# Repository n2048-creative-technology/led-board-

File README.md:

# LED board

A wall of **584 addressable pixels** — eight identical segments of 73 — that
fills with light one pixel at a time, then breathes. A Seeed XIAO ESP32C3 on a
custom 24 V driver board runs all eight segments from a single hardware timer,
and raises its own Wi-Fi access point so colour, timing and power budget can be
changed from a phone with no app and no internet.

| | |
|---|---|
| Controller | Seeed Studio XIAO ESP32C3 on the `otherworlds-v2` driver board |
| Output | 8 segments × 73 px = **584** WS281x, colour order GBR, 800 kHz, 24 V |
| Frame rate | **63 fps** with the access point running |
| Control | Wi-Fi AP `LED-Board` / `ledboard` → <http://4.3.2.1/> |
| Persistence | All settings in NVS, survive a power cycle |

---

## Contents

- [How it behaves](#how-it-behaves)
- [Web UI](#web-ui)
- [HTTP API](#http-api)
- [Driving 8 outputs from a 2-channel chip](#driving-8-outputs-from-a-2-channel-chip)
- [The driver board](#the-driver-board)
- [Firmware hardware map](#firmware-hardware-map)
- [Power](#power)
- [Build, flash, monitor](#build-flash-monitor)
- [Repository layout](#repository-layout)
- [Status](#status)

---

## How it behaves

Power-up runs a two-stage sequence, identical and in step across all eight
segments:

1. **FILL** — the segment fades up pixel by pixel from the first to the last,
   with a soft leading edge spanning a settable number of pixels.
2. **BREATHE** — once full, brightness cycles between 100% and a settable floor,
   forever.

Turning the lights off runs the fill **backwards**: the pixels withdraw in
exactly the reverse order they arrived, so the last to light is the first to go
dark. Pressing off mid-sweep picks up at the matching front position rather than
snapping, so it stays smooth even if you change your mind halfway.

The pixel levels in that diagram are not an illustration — they are computed by
running the firmware's own integer maths (`renderFrontAt()`, `breatheWave()` and
NeoPixel's gamma-2.6 table) outside the chip. The fade is gamma-corrected so it
ramps evenly to the eye instead of spending most of its apparent brightness in
the first few percent.

## Web UI

The board raises its own access point with a captive portal. Join the network
and the "sign in to network" sheet should open the UI by itself; if not, browse
to the address.

| | |
|---|---|
| SSID | `LED-Board` |
| Password | `ledboard` |
| Address | <http://4.3.2.1/> |

Everything on the page is inline — no CDN is reachable on an access point — so
the colour wheel is drawn on a `<canvas>` rather than pulled from a library.

<p align="center">
  
  &nbsp;&nbsp;
  
</p>

<sub>Left: the page as served, at its 520 px maximum width. Right: the same page
at 390 px — it is a single responsive column, which is how it will actually be
used.</sub>

### Colour

An HSV wheel (drag to pick), R/G/B sliders, a hex field, and the OS-native
colour picker. All four stay in sync, and changes are pushed to the strip live,
debounced at ~60 ms.

### Breathing and start-up fill

Period runs 0.5–20 s; a floor of 100% holds steady with no breathing. *Replay
fill* restarts the fill animation so it can be watched again without a reboot.
Edge is how many pixels the leading fade spans — 1 is a hard wipe.

### Power

The budget, with live feedback on the resulting hold level and estimated draw.
The limiter accounts for the *current colour*: red lights one channel, yellow
two, white three, so the achievable brightness changes as you pick. Read
[Power](#power) before trusting the milliamp figure on this 24 V board.

<sub>The same card at a 3000 budget (left) and 15000 with a blue-ish colour
selected (right). Both numbers come from the firmware's own estimator.</sub>

### Access point — you cannot lock yourself out

Credentials are validated server-side before being stored: SSID 1–32 characters,
password empty for an open network or 8–63 characters. A 1–7 character password
is rejected, since no access point will start with one. On top of that, if a
stored pair ever fails to bring the AP up, the board falls back to `LED-Board` /
`ledboard` by itself. **Recovering never requires reflashing over USB.**

Applying restarts the radio, so the phone will drop off and must rejoin with the
new details. The HTTP reply is sent ~400 ms before the restart, so the browser
always sees the response.

### Saving

Changes apply live. **Save to board** writes them to NVS so they survive a power
cycle; without saving, the board reverts to its defaults on reboot — including
the on/off state, so a board saved "off" comes back off.

## HTTP API

Handy for scripting or an external controller. All values are clamped
server-side, so out-of-range input is safe.

| Endpoint | Purpose |
|---|---|
| `GET /api/state` | Current settings, hold level, estimated mA, fps, phase |
| `GET /api/set?r=&g=&b=&bp=&bm=&fd=&fe=&pb=` | Set any subset; returns the new state |
| `GET /api/power?on=0\|1` | Turn off (reverse withdraw) or on (fill) |
| `GET /api/ap?ssid=&pass=` | Change AP credentials; `400` if invalid |
| `GET /api/fill` | Restart the fill animation |
| `GET /api/save` | Persist current settings to NVS |

Parameters: `r` `g` `b` 0–255 · `bp` breathe period ms 200–120000 · `bm` breathe
floor % 0–100 · `fd` fill duration ms 100–120000 · `fe` fill edge px 1–73 ·
`pb` power budget 100–40000.

`phase` reports `filling`, `breathing`, `emptying` or `off`.

```console
$ curl "http://4.3.2.1/api/state"
{"on":true,"ssid":"LED-Board","pass":"ledboard","r":255,"g":255,"b":0,
 "bp":4000,"bm":80,"fd":4000,"fe":8,"pb":3000,"hold":31,"ma":2920,
 "maFull":23944,"fps":63,"phase":"breathing"}
```

Wi-Fi does not disturb the LED output — the strips are driven by the RMT
peripheral in hardware, and the frame rate stayed at 62–63 fps with the AP up
and a client connected.

## Driving 8 outputs from a 2-channel chip

The ESP32-C3 has only **2 RMT TX channels**, which rules out both obvious
approaches. The firmware instead transmits **one** segment's worth of data on a
single RMT channel bound to GPIO3, then uses the GPIO matrix
(`esp_rom_gpio_connect_out_signal`) to route that same output signal to the
other seven pins. Every segment gets an identical, hardware-timed waveform, and
a frame costs one transmission (~2.2 ms) instead of eight.

**The trade-off:** all 8 segments necessarily show the *same* content. That is
exactly what this piece wants. If independent per-segment animation is ever
needed, the options are:

- **2 independent strips** via FastLED (the chip's real RMT limit), or
- **8 independent strips** via a parallel bit-bang driver, computing an 8-bit
  GPIO mask per bit period — all eight pins live in one 32-bit output register,
  so this is feasible but needs cycle-accurate timing work, or
- **a chip with more RMT channels** — ESP32-S3 has 4, the original ESP32 has 8.

## The driver board

KiCad project: [`electronics/otherworlds-v2.kicad_pro`](electronics/otherworlds-v2.kicad_pro).
Two-layer, **98.7 × 90.9 mm**, 1.6 mm, four M4 mounting holes, through-hole
throughout so it can be built by hand.

<sub>Exported from
<a href="electronics/otherworlds-v2.kicad_sch">otherworlds-v2.kicad_sch</a> with
<code>kicad-cli</code>. Also available as
<a href="images/schematic/otherworlds-v2.pdf">PDF</a>, and the layers as
<a href="images/schematic/pcb-front.svg">front</a> /
<a href="images/schematic/pcb-back.svg">back</a> SVG.</sub>

### Signal path

Each of the eight channels is the same four parts:

**XIAO Dn → SN74AHCT125N buffer → 220 Ω → LED connector pin 2.**

The buffers run from the on-board 5 V rail. AHCT-family logic takes a 3.3 V
input as a valid high and drives a full 5 V output, which is what gets the data
line clear of a WS281x input threshold — the XIAO's own 3.3 V swing is marginal
and fails intermittently on a long lead.

Only the data line passes through the board's logic side; **+24 V goes straight
from the Wago input to pin 3 of every LED connector** and never touches it.

### Bill of materials

From [`electronics/production/bom.csv`](electronics/production/bom.csv):

| Ref | Part | Qty | Footprint |
|---|---|---|---|
| J3, J4 | SN74AHCT125N quad buffer | 2 | DIP-14, 7.62 mm |
| R1–R8 | 220 Ω | 8 | Axial DIN0204, 5.08 mm |
| J1, J2 | 1×7 pin header — the XIAO | 2 | 2.54 mm vertical |
| J7–J14 | 1×3 pin header — LED segments 1–8 | 8 | 2.54 mm vertical |
| J15–J18 | 1×1 pin header — buck converter module | 4 | 2.54 mm vertical |
| J19 | Wago 734-132 — 24 V input | 1 | 3.50 mm vertical |
| J20 | 1×3 pin header — D0/D9/D10 breakout | 1 | 2.54 mm vertical |
| H1–H4 | M4 mounting hole, plated | 4 | 4.3 mm |

The DC-DC buck converter is a **module**, not a fitted part: it sits on the four
single-pin headers (`J18`/`J17` in, `J16`/`J15` out), so it can be sized to the
5 V load and swapped without touching the board.

`J20` breaks out D0, D9 and D10 — the three pins the LED channels do not use.
D0/GPIO2 and D9/GPIO9 are strapping pins; read
[the pinout notes](firmware/docs/xiao-esp32c3-pinout.md) before hanging anything
off them.

### Connector map

Traced through the netlist exported from the committed schematic — not read off
the drawing:

| Connector (silkscreen) | J7 (1) | J8 (2) | J9 (3) | J10 (4) | J11 (5) | J12 (6) | J13 (7) | J14 (8) |
|---|---|---|---|---|---|---|---|---|
| Net | L1 | L2 | L3 | L4 | L5 | L6 | L7 | L8 |
| Resistor | R1 | R2 | R3 | R4 | R5 | R6 | R7 | R8 |
| Buffer | J3 | J3 | J3 | J3 | J4 | J4 | J4 | J4 |
| XIAO pin | D1 | D2 | **D4** | **D3** | D5 | D6 | **D8** | **D7** |
| GPIO | 3 | 4 | 6 | 5 | 7 | 21 | 8 | 20 |

Note the two crossed pairs: J9/J10 are fed by D4/D3, and J13/J14 by D8/D7. That
is harmless here — every output carries the identical waveform, so which pin
lands on which connector cannot change what the wall does — but it is worth
knowing before probing a channel with a scope.

Every LED connector is wired the same way: **pin 1 = GND, pin 2 = data,
pin 3 = +24 V**.

> ⚠️ **The working copy of the schematic is mid-edit and currently inconsistent.**
> In `HEAD` every data label appears exactly twice (once at the XIAO header,
> once at a buffer input). In the uncommitted file, `D1` and `D2` appear only
> once each while `D7` and `D8` appear three times — the two labels at J3's
> first inputs now read D7/D8, so those buffers would be driven in parallel with
> J4's and D1/D2 would drive nothing. Because all eight channels carry the same
> waveform, the piece would still *look* correct, which is what makes it worth
> catching. The table above comes from `HEAD`; re-run
> `bash scripts-tools/export-kicad.sh` and re-check it once the edits land.

## Firmware hardware map

| | |
|---|---|
| Board | Seeed Studio XIAO ESP32C3 (`seeed_xiao_esp32c3`) |
| MCU | ESP32-C3, single-core RISC-V @ 160 MHz, 4 MB flash |
| Platform | pioarduino `espressif32` 54.3.20 — Arduino core 3.2.0, ESP-IDF 5.4 |
| LED library | Adafruit NeoPixel 1.15.5 (FastLED 3.10.3 kept for colour helpers) |
| Strip | WS281x, 800 kHz, colour order **GBR**, 24 V |
| Segments | 8 × 73 px = 584 total |
| Data pins | D1–D8 = GPIO 3, 4, 5, 6, 7, 21, 20, 8 |
| Serial | Native USB Serial/JTAG, 115200 baud |

Strip parameters (WS281x / GBR / 73) were taken from a WLED configuration
confirmed working on this exact hardware — worth keeping as the reference if
anything ever regresses. `73` counts **control ICs**, not LED packages: a 24 V
strip usually groups several physical LEDs behind each addressable pixel.

D1/GPIO3 carries the master signal because it is **not** a strapping pin, so an
attached strip cannot interfere with boot the way D0/D8/D9 could.

> **There is no GPIO22 on the ESP32-C3** — its GPIO range is 0–21. D7 is
> **GPIO20** (UART0 RX), which is what the seventh segment uses.

Full pin map, strapping-pin traps and the BOOT-button recovery procedure:
[firmware/docs/xiao-esp32c3-pinout.md](firmware/docs/xiao-esp32c3-pinout.md).

## Power

Adafruit NeoPixel has no power management of its own, so the firmware includes a
limiter: it finds the brightest scaling of the chosen colour that fits
`powerBudgetMa` and holds there, which is why the UI reports a *hold level*
rather than simply obeying the brightness you asked for.

### The estimator models a 5 V strip

> ⚠️ **The milliamp figures the firmware reports are a 5 V-strip model** —
> 20 mA per channel per pixel at full, plus 1 mA idle per controller IC. **This
> board runs the strips at 24 V**, where the current drawn from the supply is a
> different number entirely (roughly the strip's rated W/m × length ÷ 24 V).
>
> So on this hardware, treat the budget as **a brightness cap in the firmware's
> own units**, not as amps at the PSU. Size the actual supply from the strip's
> rating, measure the real draw, and then pick the budget that lands on a
> brightness you can afford.

What the limiter does with a given budget, for yellow (255, 255, 0) across all
584 pixels — these are the numbers the UI will show:

| Budget | Hold level | Fraction of full | Reported draw |
|---|---|---|---|
| 3000 (default) | 31/255 | 12% | 2920 |
| 5000 | 50/255 | 20% | 4672 |
| 10000 | 108/255 | 42% | 9928 |
| 15000 | 159/255 | 62% | 14600 |
| 20000 | 216/255 | 85% | 19856 |
| 24000+ | 255/255 | 100% | 23944 |

Colour changes the arithmetic completely. At full brightness the estimator
reports roughly **12264** for a single-channel colour (red, green, blue),
**23944** for a two-channel one (yellow, cyan, magenta) and **35624** for white
— so the same budget buys a much brighter red than white.

Whatever the voltage, two things still hold: **inject power at both ends of each
segment** (and mid-run on long ones), and expect a visible colour shift toward
red wherever the supply sags.

## Build, flash, monitor

```bash
cd firmware
pio run                    # build
pio run -t upload          # build + flash
pio device monitor         # 115200 baud
```

Last verified build (2026-08-15, `pio run`):

```
RAM:   [=         ]  11.6% (used 37944 bytes from 327680 bytes)
Flash: [========  ]  77.6% (used 1017378 bytes from 1310720 bytes)
========================= [SUCCESS] Took 12.66 seconds =========================
```

### Testing without a strip

The firmware self-reports over serial, so it can be validated with nothing
attached — the RMT peripheral will happily clock data into thin air, and the
per-2-second heartbeat reports phase, level, frame rate, estimated draw and the
number of connected Wi-Fi clients.

```
XIAO ESP32C3 - LED board
8 segments x 73 LEDs = 584 total | WS281x 800 kHz, order GBR
Pins: D1=GPIO3 D2=GPIO4 D3=GPIO5 D4=GPIO6 D5=GPIO7 D6=GPIO21 D7=GPIO20 D8=GPIO8
  RMT signal 87 on GPIO3 -> mirrored to: GPIO4 GPIO5 GPIO6 GPIO7 GPIO21 GPIO20 GPIO8
Colour 255,255,0 | budget 3000 mA -> hold 31/255 (est. 2920 mA, full 23944 mA)
AP "LED-Board" up -> http://4.3.2.1/  (password: ledboard)
PHASE: FILL
[    2000 ms] FILL    | level  31/255 | 62 fps | est. 2920 mA | clients 0
PHASE: BREATHE
[    4000 ms] BREATHE | level  27/255 | 63 fps | est. 2607 mA | clients 1
```

<sub>Format derived from the <code>Serial.printf</code> calls in
<code>main.cpp</code>; the RMT signal number is whatever the driver was
assigned. Not yet captured from hardware — see <a href="#status">Status</a>.</sub>

Three things to check first if something looks wrong:

- **Garbled colours or flicker** → wrong chipset timing. `PIXEL_TYPE` is
  `NEO_GBR + NEO_KHZ800`.
- **Colours swapped** (yellow shows as something else) → wrong byte order. Swap
  the letters in the `NEO_GBR` half of `PIXEL_TYPE`; common variants are `GRB`,
  `RGB` and `BRG`.
- **`FAN-OUT FAILED: GPIO3 has no peripheral signal`** → the RMT channel never
  bound to the master pin, so only segment 1 would light. Everything downstream
  depends on that line succeeding.

## Repository layout

```
electronics/          KiCad project "otherworlds-v2" — schematic, PCB, production files
  production/         Gerbers, BOM, positions (JLCPCB fabrication toolkit output)
firmware/             PlatformIO project
  src/main.cpp        the whole firmware: animation, power limiter, AP, web UI
  docs/               pinout and GPIO caveats
images/
  diagrams/           SVG diagrams (generated)
  schematic/          KiCad exports + the 3D render
  webui/              web UI screenshots (generated)
scripts-tools/        the generators for everything in images/
```

### Regenerating the documentation assets

All three generators are deterministic; only the KiCad exports need KiCad
installed, and none of them need hardware:

```bash
python3 scripts-tools/mkshots.py      # -> images/webui/*.png
python3 scripts-tools/mkdiagrams.py   # -> images/diagrams/*.svg
bash    scripts-tools/export-kicad.sh # -> images/schematic/*
```

`mkshots.py` lifts the page straight out of the `R"HTML(...)HTML"` literal in
`firmware/src/main.cpp`, replaces `window.fetch` with a shim that reimplements
the `/api/*` handlers — including the integer power maths — and screenshots the
result in headless Chrome. So the screenshots track the firmware: change the UI,
re-run, and the README is current. `mkdiagrams.py` likewise computes the
animation diagram from the firmware's own rendering maths. Details in
[scripts-tools/README.md](scripts-tools/README.md).

## Status

| Step | Status |
|---|---|
| PCB designed, fabrication files exported | ✅ `otherworlds-v2`, July 2026 |
| Builds for `seeed_xiao_esp32c3` | ✅ 2026-08-15 — RAM 11.6%, flash 77.6% |
| Web UI rendered and exercised | ✅ against a faithful mock of the device API |
| Flashed and run on hardware | ⏳ pending — no board on USB at time of writing |
| Board brought up with strips attached | ⏳ pending |
| Measured current draw | ⏳ pending — all power figures are estimates, and the estimator assumes 5 V |

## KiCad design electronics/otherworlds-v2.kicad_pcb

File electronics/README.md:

# Electronics — `otherworlds-v2`

KiCad 9 project for the LED driver board: a XIAO ESP32C3 carrier that buffers
its eight data outputs to 5 V and hands them to eight 24 V LED segments.

Open [`otherworlds-v2.kicad_pro`](otherworlds-v2.kicad_pro). Rendered exports of
the schematic and layers live in [`../images/schematic/`](../images/schematic)
and are regenerated with `bash ../scripts-tools/export-kicad.sh`.

| | |
|---|---|
| Size | 98.7 × 90.9 mm, 1.6 mm, 2 layer |
| Mounting | 4 × M4 plated holes (H1–H4) |
| Assembly | Through-hole throughout — hand-solderable |
| Input | 24 V via Wago 734-132 (J19) |
| Logic supply | DC-DC buck module on J15–J18, 24 V → 5 V |

## Signal path

Eight identical channels:

```
XIAO Dn ─► SN74AHCT125N (J3 for D1-D4, J4 for D5-D8) ─► 220 Ω (Rn) ─► LED connector pin 2
```

AHCT logic runs from 5 V and accepts 3.3 V as a valid high, so it both level
shifts and buffers: the strip sees a full 5 V edge instead of the XIAO's
marginal 3.3 V. The series resistor damps reflections and sits at the driver
end of the line.

+24 V runs from J19 straight to pin 3 of every LED connector. It never enters
the logic side of the board.

## Connector map

Traced through the netlist of the committed schematic:

| Connector | J7 (1) | J8 (2) | J9 (3) | J10 (4) | J11 (5) | J12 (6) | J13 (7) | J14 (8) |
|---|---|---|---|---|---|---|---|---|
| Net | L1 | L2 | L3 | L4 | L5 | L6 | L7 | L8 |
| Resistor | R1 | R2 | R3 | R4 | R5 | R6 | R7 | R8 |
| Buffer | J3 | J3 | J3 | J3 | J4 | J4 | J4 | J4 |
| XIAO pin | D1 | D2 | **D4** | **D3** | D5 | D6 | **D8** | **D7** |
| GPIO | 3 | 4 | 6 | 5 | 7 | 21 | 8 | 20 |

J9/J10 and J13/J14 are fed by crossed pairs. Harmless — the firmware drives all
eight outputs with one identical waveform — but worth knowing at the bench.

LED connectors are all **pin 1 = GND, pin 2 = data, pin 3 = +24 V**.

> ⚠️ The working copy is currently mid-edit: `D1`/`D2` appear once each and
> `D7`/`D8` three times, i.e. J3's first two inputs are labelled D7/D8 rather
> than D1/D2. In `HEAD` every label appears exactly twice. See the root
> [README](../README.md#connector-map).

Other headers:

| Ref | Purpose |
|---|---|
| J1 / J2 | XIAO ESP32C3, 1×7 each |
| J15–J18 | Buck module: J18/J17 = 24 V in, J16/J15 = 5 V out |
| J19 | 24 V input, Wago cage clamp |
| J20 | Breakout of the three unused pins: D0, D9, D10 |

⚠️ D0/GPIO2 and D9/GPIO9 on J20 are **strapping pins**. Anything wired there can
stop the board booting — read
[../firmware/docs/xiao-esp32c3-pinout.md](../firmware/docs/xiao-esp32c3-pinout.md)
first.

## Fabrication

[`production/`](production) holds the JLCPCB fabrication-toolkit output:
[`otherworlds-v2.zip`](production/otherworlds-v2.zip) (gerbers),
[`bom.csv`](production/bom.csv), [`positions.csv`](production/positions.csv),
[`designators.csv`](production/designators.csv) and an IPC netlist. Settings are
in [`fabrication-toolkit-options.json`](fabrication-toolkit-options.json).

Everything is through-hole, so the BOM carries no LCSC part numbers — it is a
hand-assembly list, not an assembly-service one.

## Sizing the supply

Work from the strip's rating, not from the firmware's estimate: the firmware's
milliamp figures model a 5 V strip, while these segments run at 24 V. Take the
strip's W/m × total length ÷ 24 V, add margin, and fuse the input. Inject at
both ends of each segment.

Details, and what the firmware's budget number actually controls, in the root
[README](../README.md#power).

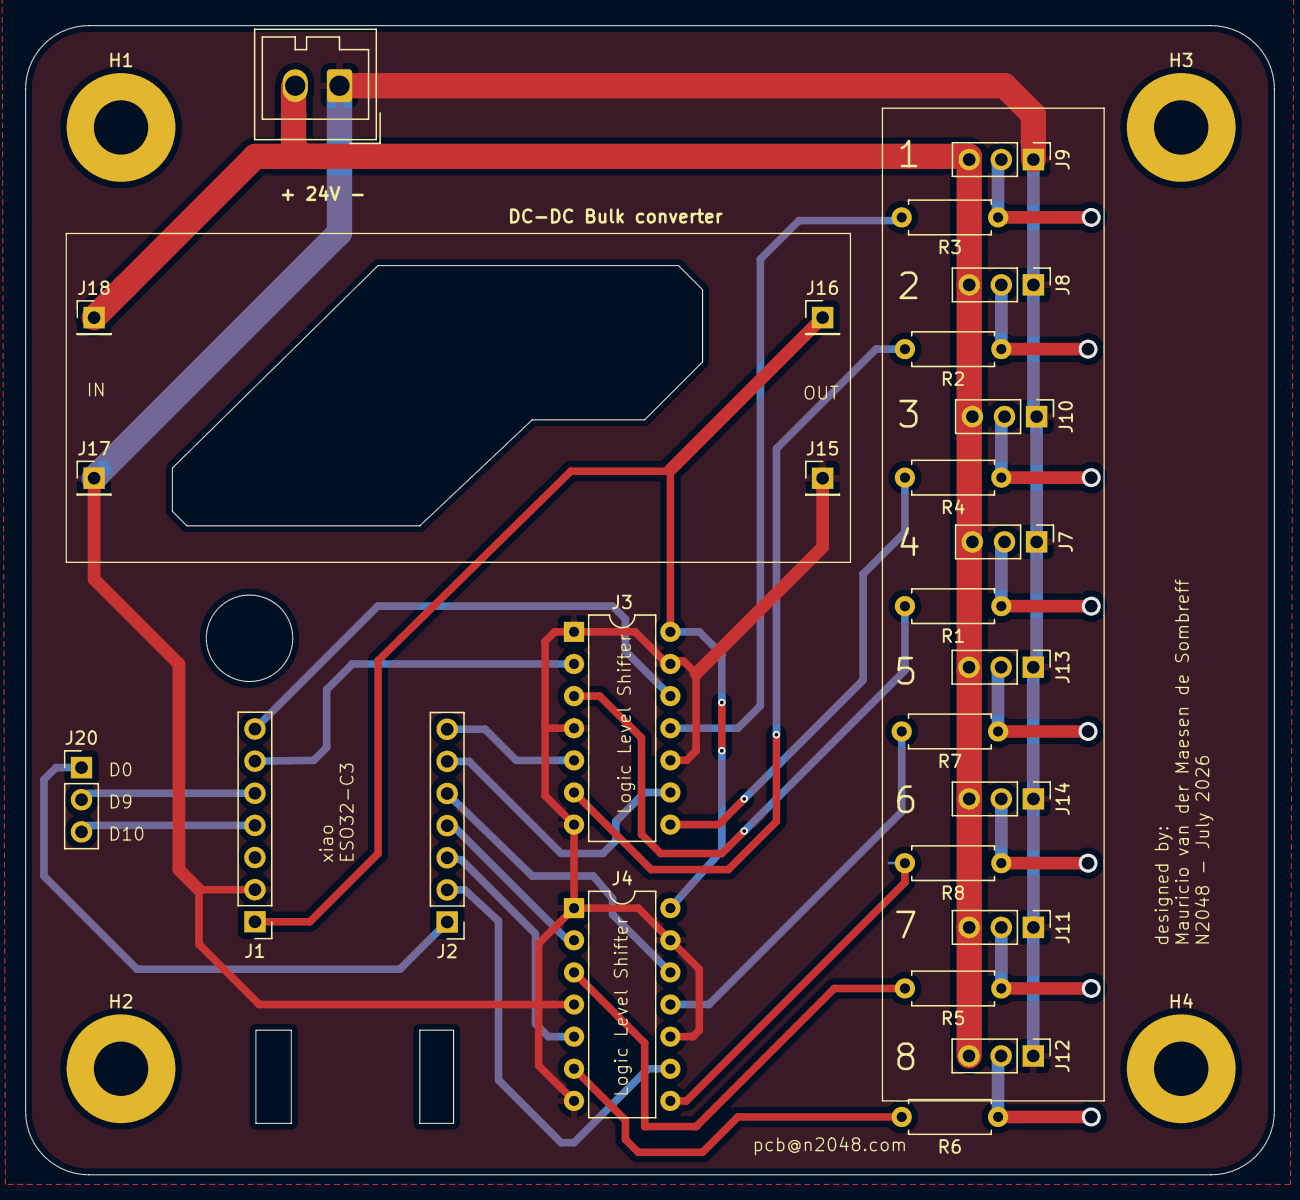
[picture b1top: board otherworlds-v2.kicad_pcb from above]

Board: 2 copper layers, 98.7 x 90.9 mm, 30 parts (0 on the bottom side), 30 nets.

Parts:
H1, H2, H3, H4: MountingHole_Pad_MP; MountingHole_4.3mm_M4_Pad
J1, J2: Conn_01x07; PinHeader_1x07_P2.54mm_Vertical
J3, J4: SN74AHCT125N; DIP-14_W7.62mm
J7: LED1; PinHeader_1x03_P2.54mm_Vertical
J8: LED2; PinHeader_1x03_P2.54mm_Vertical
J9: LED3; PinHeader_1x03_P2.54mm_Vertical
J10, J20: LED4; PinHeader_1x03_P2.54mm_Vertical
J11: LED5; PinHeader_1x03_P2.54mm_Vertical
J12: LED6; PinHeader_1x03_P2.54mm_Vertical
J13: LED7; PinHeader_1x03_P2.54mm_Vertical
J14: LED8; PinHeader_1x03_P2.54mm_Vertical
J15, J17: GND; PinHeader_1x01_P2.54mm_Vertical
J16: 5V; PinHeader_1x01_P2.54mm_Vertical
J18: 24V; PinHeader_1x01_P2.54mm_Vertical
J19: Conn_01x02; Wago_734-132_1x02_P3.50mm_Vertical
R1, R2, R3, R4, R5, R6, R7, R8: 220; R_Axial_DIN0207_L6.3mm_D2.5mm_P7.62mm_Horizontal

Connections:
+5V: J1.1, J3.14 (VCC), J4.14 (VCC), J16.1
+24V: J7.3, J8.3, J9.3, J10.3, J11.3, J12.3, J13.3, J14.3, J18.1, J19.2
/D0: J2.1, J20.1
/D1: J2.2, J4.9 (3A)
/D2: J2.3, J4.5 (2A)
/D3: J2.4, J4.2 (1A)
/D4: J2.5, J4.12 (4A)
/D5: J2.6, J3.9 (3A)
/D6: J2.7, J3.5 (2A)
/D7: J1.7, J3.12 (4A)
/D8: J1.6, J3.2 (1A)
/D9: J1.5, J20.2
/D10: J1.4, J20.3
/L1: J7.2, R1.1
/L2: J8.2, R2.1
/L3: J9.2, R3.1
/L4: J10.2, R4.1
/L5: J11.2, R5.1
/L6: J12.2, R6.1
/L7: J13.2, R7.1
/L8: J14.2, R8.1
GND: J1.2, J3.1 (1/OE), J3.4 (2/OE), J3.7 (GND), J3.10 (3/OE), J3.13 (4/OE), J4.1 (1/OE), J4.4 (2/OE), J4.7 (GND), J4.10 (3/OE), J4.13 (4/OE), J7.1, J8.1, J9.1, J10.1, J11.1, J12.1, J13.1, J14.1, J15.1, J17.1, J19.1
unnamed: J3.3 (1Y), R1.2
unnamed: J3.6 (2Y), R2.2
unnamed: J3.8 (3Y), R4.2
unnamed: J3.11 (4Y), R3.2
unnamed: J4.3 (1Y), R5.2
unnamed: J4.6 (2Y), R6.2
unnamed: J4.8 (3Y), R8.2
unnamed: J4.11 (4Y), R7.2

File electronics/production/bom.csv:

Designator,Footprint,Quantity,Value,LCSC Part #
"H1, H2, H3, H4",MountingHole_4.3mm_M4_Pad,4,MountingHole_Pad_MP,
"J1, J2",PinHeader_1x07_P2.54mm_Vertical,2,Conn_01x07,
"J10, J20",PinHeader_1x03_P2.54mm_Vertical,2,LED4,
J11,PinHeader_1x03_P2.54mm_Vertical,1,LED5,
J12,PinHeader_1x03_P2.54mm_Vertical,1,LED6,
J13,PinHeader_1x03_P2.54mm_Vertical,1,LED7,
J14,PinHeader_1x03_P2.54mm_Vertical,1,LED8,
"J15, J17",PinHeader_1x01_P2.54mm_Vertical,2,GND,
J16,PinHeader_1x01_P2.54mm_Vertical,1,5V,
J18,PinHeader_1x01_P2.54mm_Vertical,1,24V,
J19,Wago_734-132_1x02_P3.50mm_Vertical,1,Conn_01x02,
"J3, J4",DIP-14_W7.62mm,2,SN74AHCT125N,
J7,PinHeader_1x03_P2.54mm_Vertical,1,LED1,
J8,PinHeader_1x03_P2.54mm_Vertical,1,LED2,
J9,PinHeader_1x03_P2.54mm_Vertical,1,LED3,
"R1, R2, R3, R4, R5, R6, R7, R8",R_Axial_DIN0207_L6.3mm_D2.5mm_P7.62mm_Horizontal,8,220,
